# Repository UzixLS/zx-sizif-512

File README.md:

## Sizif-512
Another CPLD-based ZX Spectrum clone for 48K rubber case with some sweet features.

### Tech specs
* Half-sized PCB for 48K rubber case
* Pentagon, Spectrum 128, Spectrum 48 and Spectrum +3e modes
* Altera EPM1270 CPLD
* Real Z80 in 3.5MHz, 4.4MHz, 5.2MHz, 7MHz (no-wait turbo) and 14MHz (turbo with wait-states) modes
* 512K RAM
* Real AY-3-8910 with switchable stereo ABC/ACB/mono output
* Sega 6-button joystick input; Kempston/Sinclair modes
* Integrated DivMMC and Z-Controller, 1x microSD socket
* PAL and RGB video output (Sega Mini-DIN/9 connector)
* Digital video output header for EGA monitors, VGA scandoublers, etc.
* ULAplus
* Timex MultiColor and HiRes support
* Mono covox (Pentagon ans SpecDrum standards)
* SounDrive (4-channel stereo covox)
* WiFi addon ([link](https://github.com/UzixLS/zx-sizif-512-wifi))
* Tape input via 3.5" jack and Bluetooth
* 9-12V power supply with any polarity
* Reset and Magic buttons; header for power button

With extension board ([link](https://github.com/UzixLS/zx-sizif-512-ext)) more features may be added:
* Turbo Sound FM
* General Sound (12MHz / 512Kb RAM)
* SAA1099
* MIDI sound

### Demonstration
Running Pentagon and Spectrum 128 demos: [link](https://www.youtube.com/watch?v=_RoLKcfJSTY) \
Playing music from SD: [link](https://www.youtube.com/watch?v=TmikKD3yqOU) \
Some random photos: [link](https://cloud.err200.net/index.php/s/73TR85tYZkMm8Ax?path=%2Fsizif-512) \
Review by Martin's 8-bit blog (in czech): [link](https://www.8bity.cz/2020/zx-spectrum-clone-with-cpld-ulaplus-sizif-512/#) \
Review by The Retro Shack youtube channel: [link](https://www.youtube.com/watch?v=l5IgQTgq_bg) \
Building from scratch experience in Terence Ang's blog: [part1](https://www.terenceang.com/2021/08/28/building-a-zx-spectrum-clone-in-2021-begining/) [part2](https://www.terenceang.com/2021/08/29/building-a-zx-spectrum-clone-in-2021-sourcing-for-parts/) [part3](https://www.terenceang.com/2021/08/31/building-a-zx-spectrum-clone-in-2021-populating-the-board/)

### Magic button
Sizif has a number of configurable parameters that you can change on the fly. To do this just hold Magic button for a second.

To navigate menu you can use up-down keys, to change value use enter or left-right keys. Kempston, Sinclair, Cursor and QAOP supported.

If you press Magic button for a short time, the standard NMI handler 'll be called.

### Sega gamepad buttons
Sega gamepad support will be available starting from PCB rev.D (or Rev.C with slight modifications).
| Button | Function in Kempston mode | Function in Sinclair mode |
| - | - | - |
| Right | Right (bit 0) | 7 |
| Left | Left (bit 1) | 6 |
| Down | Down (bit 2) | 8 |
| Up | Up (bit 3) | 9 |
| A | Button 3 (bit 6) | N |
| B | Button 1 (bit 4) | 0 |
| C | Button 2 (bit 5) | M |
| X | Turbo Button 3 (bit 6) | Turbo N |
| Y | Turbo Button 1 (bit 4) | Turbo 0 |
| Z | Turbo Button 2 (bit 5) | Turbo M |
| Start | Pause | Pause |
| Mode | Magic button | Magic button |

### PS/2 keyboard buttons
| Button | Function |
| - | - |
| F1 | Pause |
| F2 | Fast forward |
| F5 | Magic button |
| F10 | Reboot |
| F12 | Reboot |
| Ctrl+Alt+Del | Reboot |
| Ctrl+Alt+Backspace | Reboot |
| Numpad 8, 2/5, 4, 6 | Joystick's up-down-left-right |
| Numpad 0/Enter | Joystick's fire |
| Alt | Joystick's fire |

### RAM
Sizif contains 512K RAM. There are two cases how to access it:
1. DivMMC enabled (SD card insert) - 128K available via 7FFDh port, 128K via DFFDh (Profi standart, most compatible with old 128K software) and 128K reserved for DivMMC.
2. No SD card present - 128K available via 7FFDh and 384K via DFFDh. Please note: ULAplus and Magic button shares one page of memory with DFFD port. If you run 512K-software, it's good idea not to use ULAplus and Magic.

Note that DFFDh port available only in Pentagon mode.

### SD card
Sizif have preinstalled esxDOS firmware, which provides ability to load TAP, TRD, SCL, Z80 files and save snapshots. To use this you should format SD cart to FAT32 or FAT16 and unpack latest esxDOS release ([link](http://www.esxdos.org/index.html)) to card. Also it's recommended to install Long Filename Browser ([link](https://spectrumcomputing.co.uk/forums/viewtopic.php?t=2553)) to card.

### Timex 2048 MultiColor and HiRes support
The Timex graphics modes added by amsoft78.
Basic ways to setup Timex 2048 modes is:
* OUT 255, 1 - use Timex Screen #1 from 0x6000 instead of 0x4000
* OUT 255, 2 - sets HiColor mode. Screen bitmap is read from 0x4000, but screen attributes are read from 0x6000. Each 8x1 bitmap has separate attributes entry, in opposite to 8x8 in regular Zx Spectrum.
* OUT 255, 6 - sets HiRes mode. Screen is now 512x192 in two colors. Both Screen #0 from 0x4000 (odd columns) and 0x6000 (even columns) contains bitmap. Bits 5 to 3 in port 0xFF defines the ink color common for the whole screen. Background colour is always its binary inversion.
* OUT 255, 0 - sets the regular ZX Spectrum mode.

To activate Timex modes, the followig ports can be used:
* ZX eLeMeNt compatible port 0x9FFD - shadowing original Timex 0xFF port, but with read and write capabilities.
* ULA+ compatible method - on port 0xBF3B and "ModeGrop" (bits 7:6 == "01"). See Ula+ specification, as the values are different than for port 0xFF. Warning! As the lot of software first sets the Timex mode by 0xFF, and then sets "01000000" value in 0xBF3B, it would reset Timex mode back to 0. So this combination is ignored - no possibiity to turn off Timex modes via Ula+ port.
* oryginal Timex 0xFF port - write only. This preserves original ZX Spectrum "Floating Bus", so the port is write-only.

Warning! The method of binary "or" current 0xFF port value, somewhere adviced to use on original Timex 2048, will not work properly:

```
in      a, (0xFF)
or      a, 2
out     (0xFF), a
```

### Tested addons
* [AYX-32](https://github.com/tslabs/arm/tree/master/AYX-32) - OK
* BDI-ZX ver 2.0 MVcomp FDD interface - OK
* [ZX Dandanator! Mini 2.1](http://www.dandare.es/Proyectos_Dandare/ZX_Dandanator%21_Mini_EN.html) - OK
* [ZX TSid](https://github.com/UzixLS/zx-tsid) - OK
* [Multiface 128 1.00 by Steve Smith](http://projectspeccy.com/projects/) - OK (if SD card isn't insert)
* Noname +3DOS floppy controller - OK (since rev.D)
* [PLUS 2A FDD Interface](https://github.com/konkotgit/PLUS-2A-FDD) - OK (since rev.D)
* DivIDE 5.7d - OK (if SD card isn't insert)
* DMA 2.02 by ShamaZX - OK
* [Kempston + TurboSound interface](https://github.com/konkotgit/KTS) - OK
* [ZX-HD](https://www.bytedelight.com/?page_id=1800) - OK
* [ZX-VGA-JOY](http://zx-vga-joy.com/) - OK
* [Spectranet by ByteDelight](https://www.bytedelight.com/?page_id=3515) - OK
* Spectranet by ShamaZX (aka ZX Net 512) - OK
* ZXKit1 VGA converter (with [alternative firmware](https://github.com/UzixLS/zxkit1-vga-scandoubler-firmware)) - OK

### Changelog & current status
* Rev.A - first release. Please note the [errata](pcb/rev.A/ERRATA.ru.txt) (in russian).
* Rev.B - abandoned. Files kept for historical reason.
* Rev.C - BDI has been removed; improved video circuit; more capable CPLD; better power circuit; add mono AY mode. [Errata](pcb/rev.C/ERRATA.txt).
* Rev.C1 - fixed incorrect JTAG pinout; fixed incorrect silkscreen for power connector J3, tuned some circuit values. Everything seems to work. [Errata](pcb/rev.C1/ERRATA.txt).
* Rev.D:
    * added zxbus connector for in-case addons
    * added support for +3DOS floppy controller
    * added support for Sega 3/6-button gamepad
    * added PS/2
    * added Bluetooth tape input (via M18 module)
    * added alternative microSD card socket footprint
    * fixed compatibility with some keyboards
    * modified tape input circuit
* Rev.D1: minor changes in pcb layout
* Rev.E:
    * added fuse on power input
    * added protection diode on 5V power rail
    * rotated left keyboard connector by 180 degrees
    * replaced TRS audio connectors by TRRS with video output
    * changed C37,C38,C39 footprint to able to install film capacitors
    * improved compatibility with wireless sega gamepads - 3.3V power replaced by 5V
    * added ability to simultaneously install the power/reset keys together with the connectors
    * added jumper for wiring minidin-9 pin 4 with composite or sync output for compatibility with dirty scart cables
    * added ability to install full-height 4.43MHz crystal
    * all 0.5/0.3 vias replaced by 0.6/0.3
    * experimental: 74HCU04-based speaker amplifier replaced by LM386-based
    * experimental: 74HCU04-based tape input circuit replaced by LM311-based
    * experimental: 74HCU04-based crystal clock generator replaced by ICS501-based
* Rev.E1:
    * reverted experimental rev.E changes

### Acknowledgments
This work is inspired and based on a lot of other projects and would hardly have been successful without them:
* Harlequin ([link](https://www.facebook.com/groups/349470902442395/))
* Karabas-128 ([link](https://github.com/andykarpov/karabas-128))
* ZX Evolution ([link](http://nedopc.com/zxevo/zxevo.php))
* zx_ula verilog implementation ([link](https://opencores.org/projects/zx_ula))

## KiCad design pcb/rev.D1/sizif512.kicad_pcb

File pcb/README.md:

* Rev.A - please see [errata (in russian)](rev.A/ERRATA.ru.txt)
* Rev.B - work in progress

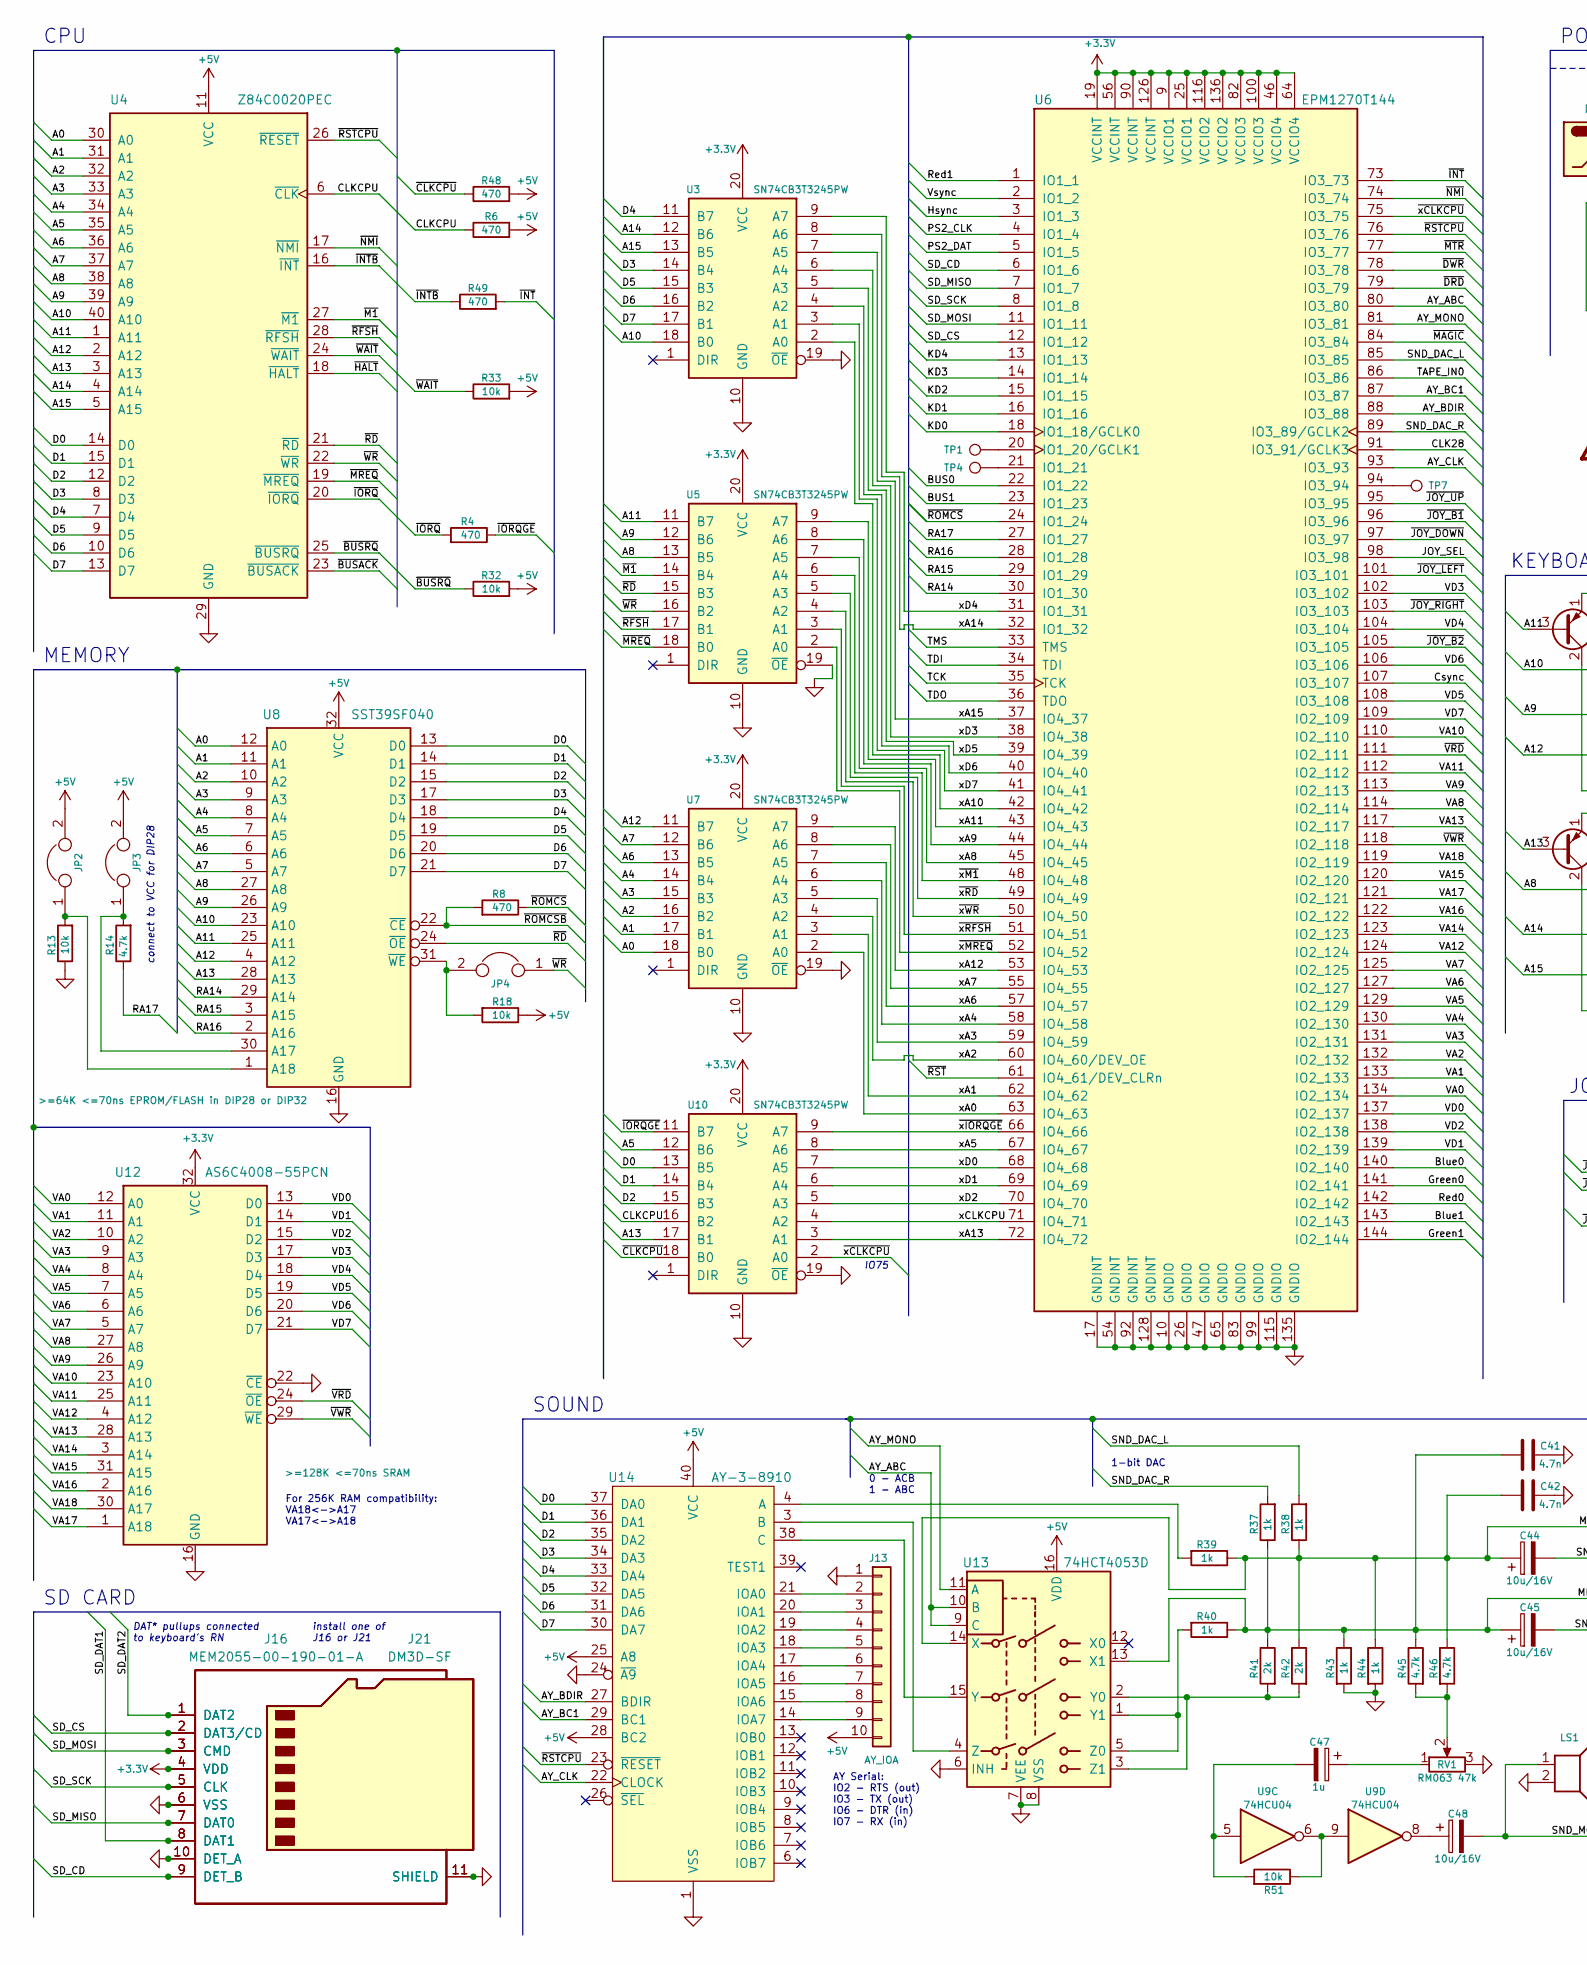
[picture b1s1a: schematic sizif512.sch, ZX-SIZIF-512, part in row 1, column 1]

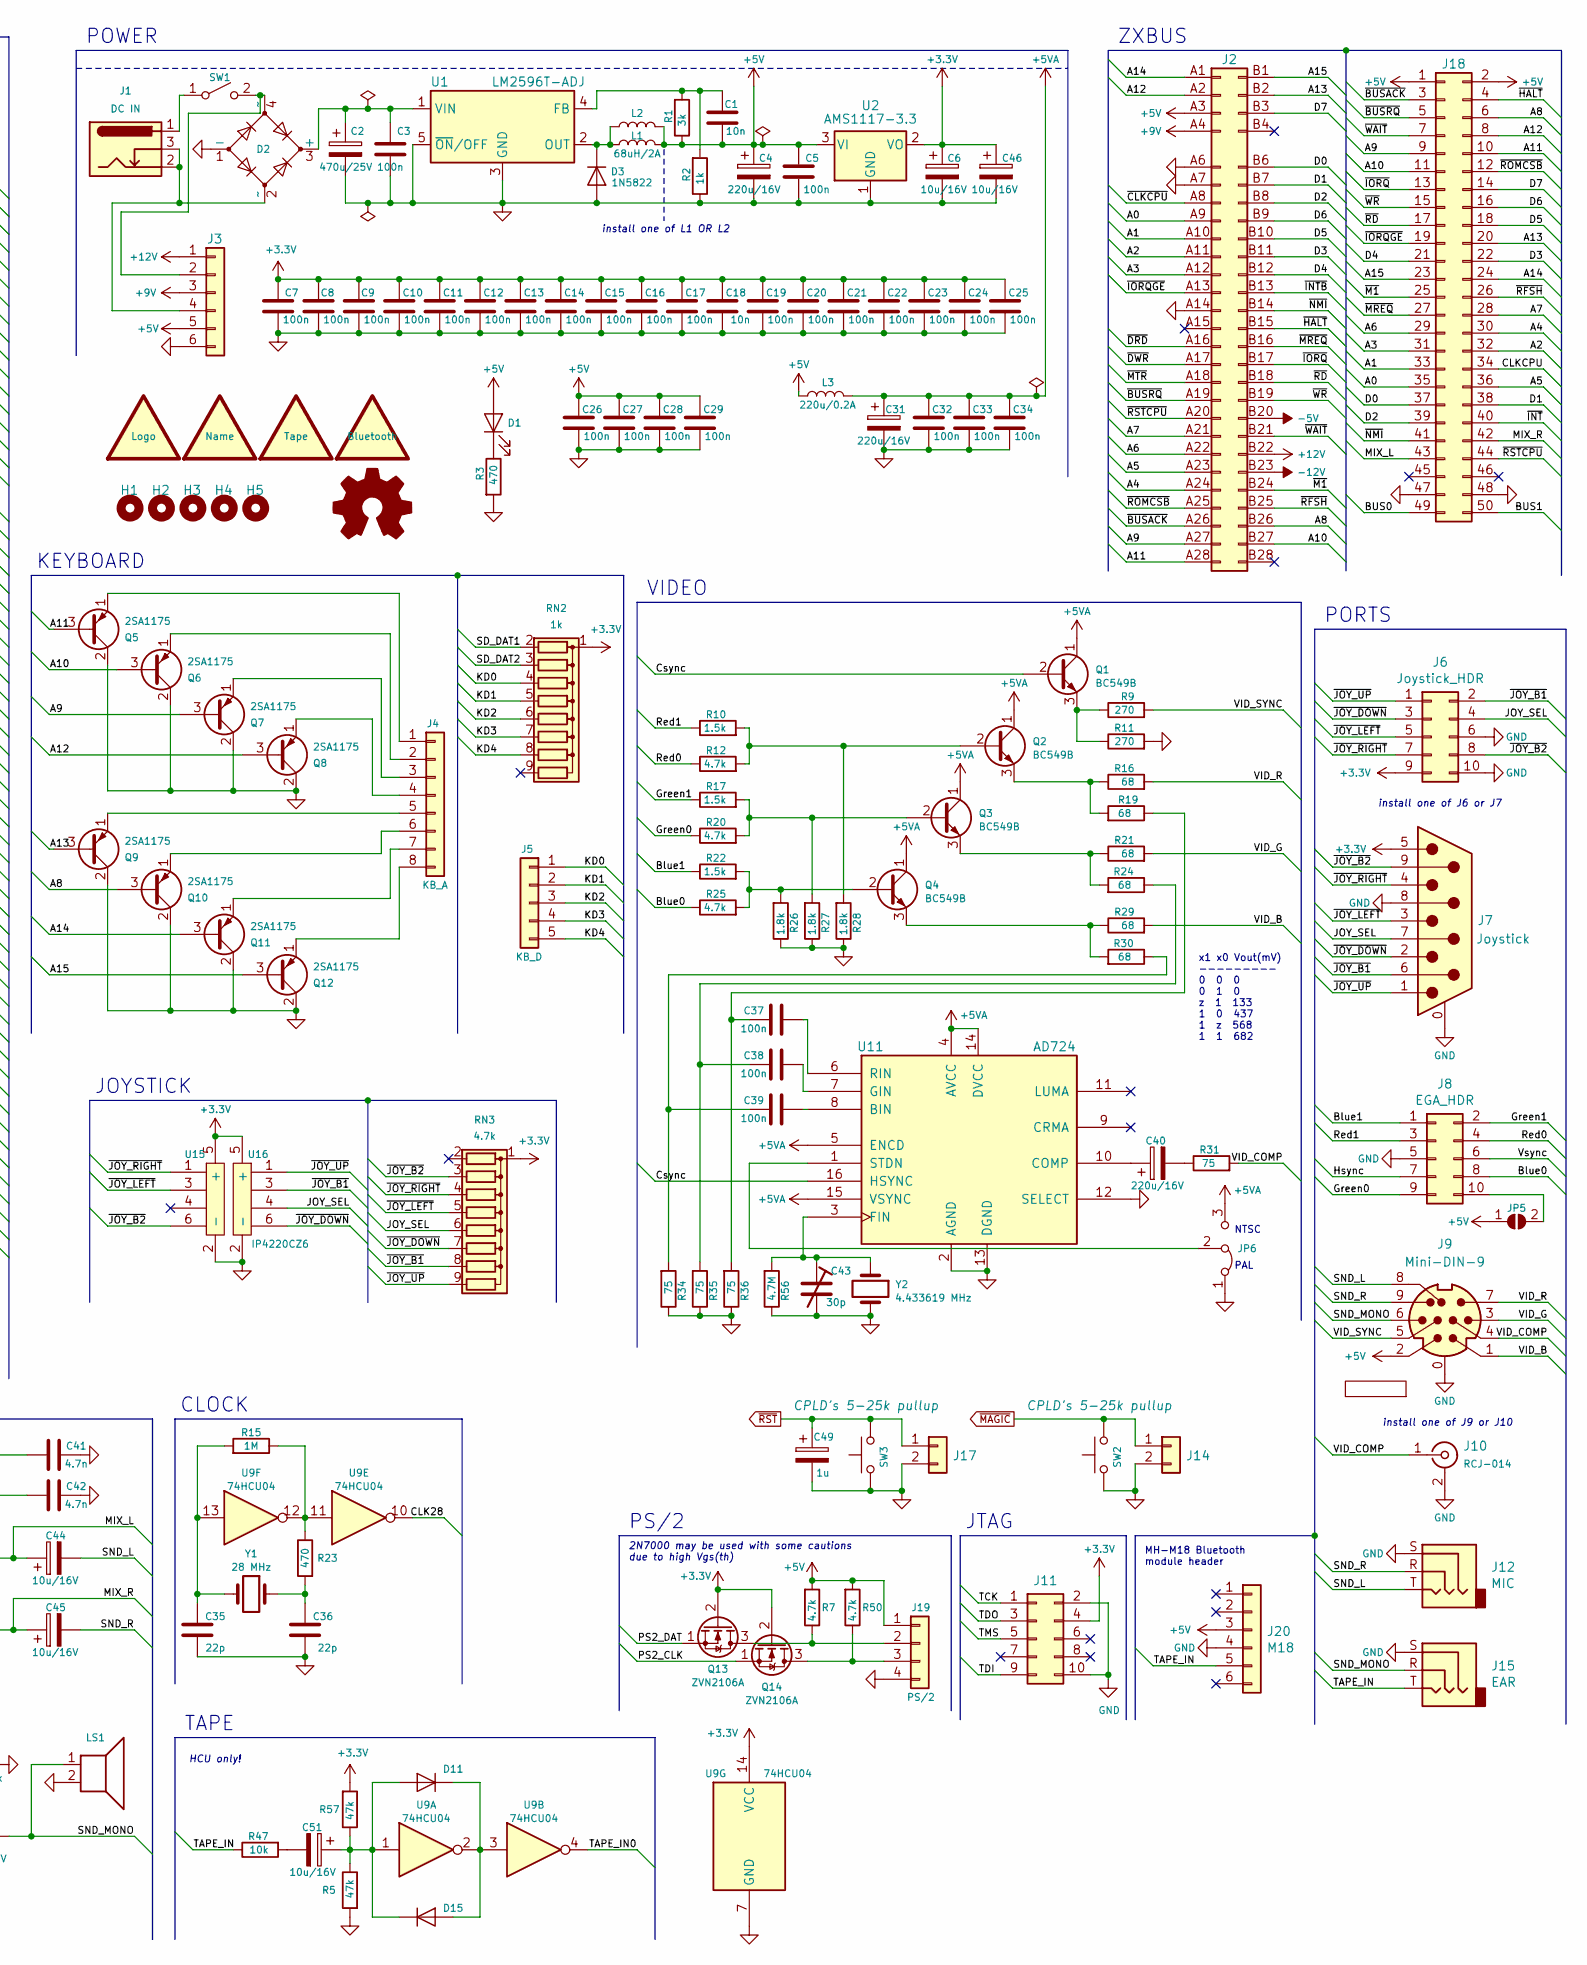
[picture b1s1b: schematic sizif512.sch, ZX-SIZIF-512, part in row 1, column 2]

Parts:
C1: 10n; C_Disc_D5.0mm_W2.5mm_P2.50mm
C2: 470u/25V; CP_Radial_D10.0mm_P5.00mm
C3, C7, C26, C28, C32, C33, C34, C37, C38, C39: 100n; C_Disc_D5.0mm_W2.5mm_P2.50mm
C4, C31: 220u/16V; CP_Radial_D8.0mm_P3.50mm
C5, C8, C9, C10, C11, C12, C13, C14, C15, C16, C17, C19, C20, C21, C22, C23, C24, C25, C27, C29: 100n; C_0805_2012Metric_Pad1.15x1.40mm_HandSolder
C6, C44, C45, C46, C48, C51: 10u/16V; CP_Radial_D5.0mm_P2.00mm
C18: 10n; C_0805_2012Metric_Pad1.15x1.40mm_HandSolder
C35, C36: 22p; C_Disc_D3.8mm_W2.6mm_P2.50mm
C40: 220u/16V; CP_Radial_D6.3mm_P2.50mm
C41, C42: 4.7n; C_Disc_D5.0mm_W2.5mm_P2.50mm
C43: 30p; C_Trim_D6.3mm_P5.50mm
C47, C49: 1u; CP_Radial_D4.0mm_P2.00mm
D1: LED; LED_D4.0mm
D2: 2W10; Diode_Bridge_Round_D10.0mm
D3: 1N5822; D_DO-201AD_P5.08mm_Vertical_AnodeUp
D11, D15: 1N4148; D_DO-35_SOD27_P2.54mm_Vertical_AnodeUp
H1, H2: MountingHole; MountingHole_5mm_7mm_fence
H3, H4, H5: MountingHole; MountingHole_3mm
J1: DS-210; BarrelJack_Horizontal
J2: Conn_02x28_Row_Letter_First; ZX_EDGE
J3, J20: Pin header 1x6 Pitch=2.54mm; PinHeader_1x06_P2.54mm_Vertical
J4: DS1020-08; FFC_FPC_1x08
J5: DS1020-05; FFC_FPC_1x05
J6, J8, J11: Pin header 2x5 Pitch=2.54mm; PinHeader_2x05_P2.54mm_Vertical
J7: DB9-M; DSUB-9_Male_Horizontal_P2.77x2.84mm_EdgePinOffset4.94mm_Hou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
J9: Mini-DIN-9; minidin-9
J10: RCJ-014; CUI_RCJ-01X-WIDE
J12, J15: PJ-313
J13: Pin header 1x10 Pitch=2.54mm; PinHeader_1x10_P2.54mm_Vertical
J14, J17: Pin header 1x2 Pitch=2.54mm; PinHeader_2x01_P2.54mm_Vertical
J16: MEM2055-00-190-01-A; GCT-MEM2055-00-190-01-A
J18: Pin socket 3x25 or 2xPin socket 1x25 Pitch=1.27mm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; PinHeader_2x25_P1.27mm_Edge_SMD
J19: Pin header 1x4 Pitch=2.54mm; PinHeader_1x04_P2.54mm_Vertical
J21: DM3D-SF; microSD_HC_Hirose_DM3D-SF
JP2, JP3, JP4: Jumper / Pin header 1x2 Pitch=2.54mm; PinHeader_1x02_P2.54mm_Vertical
JP5: SolderJumper_2_Open; SolderJumper-2_P1.3mm_Open_RoundedPad1.0x1.5mm
JP6: Jumper_3_Bridged12; SolderJumper-3_P1.3mm_Bridged12_RoundedPad1.0x1.5mm_NumberL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
L1: 68uH/2A; L_Radial_D8.7mm_P5.00mm_Fastron_07HCP
L2: 68uH/2A; L_12x12mm_H8mm
L3: 220u/0.2A; L_Radial_D8.7mm_P5.00mm_Fastron_07HCP
LOGO1: graphic; black-mage2
LOGO2: Logo_Open_Hardware_Small; OSHW-Symbol_6.7x6mm_SilkScreen
LOGO3: graphic; jack35
LOGO4: graphic; bluetooth_small
LOGO5: graphic; sizif512
LS1: Pin header 1x2 Pitch=2.54mm; PinHeader_1x02_P2.54mm_Vertical
Q1, Q2, Q3, Q4: BC549B; TO-92
Q5, Q6, Q7, Q8, Q9, Q10, Q11, Q12: 2SA1175; TO-92S
Q13, Q14: ZVN2106A; TO-92
R1: 3k; R_Axial_DIN0207_L6.3mm_D2.5mm_P2.54mm_Vertical
R2: 1k; R_Axial_DIN0207_L6.3mm_D2.5mm_P2.54mm_Vertical
R3, R23: 470; R_Axial_DIN0207_L6.3mm_D2.5mm_P2.54mm_Vertical
R4, R6, R8, R48, R49: 470; R_Axial_DIN0207_L6.3mm_D2.5mm_P7.62mm_Horizontal
R5, R57: 47k; R_Axial_DIN0207_L6.3mm_D2.5mm_P2.54mm_Vertical
R7, R12, R20, R25, R50: 4.7k; R_Axial_DIN0207_L6.3mm_D2.5mm_P2.54mm_Vertical
R9, R11: 270; R_Axial_DIN0207_L6.3mm_D2.5mm_P2.54mm_Vertical
R10, R17, R22: 1.5k; R_Axial_DIN0207_L6.3mm_D2.5mm_P2.54mm_Vertical
R13, R18, R32, R33: 10k; R_Axial_DIN0207_L6.3mm_D2.5mm_P7.62mm_Horizontal
R14, R45, R46: 4.7k; R_Axial_DIN0207_L6.3mm_D2.5mm_P7.62mm_Horizontal
R15: 1M; R_Axial_DIN0207_L6.3mm_D2.5mm_P2.54mm_Vertical
R16, R19, R21, R24, R29, R30: 68; R_Axial_DIN0207_L6.3mm_D2.5mm_P2.54mm_Vertical
R26, R27, R28: 1.8k; R_Axial_DIN0207_L6.3mm_D2.5mm_P2.54mm_Vertical
R31, R34, R35, R36: 75; R_Axial_DIN0207_L6.3mm_D2.5mm_P2.54mm_Vertical
R37, R38, R39, R40, R43, R44: 1k; R_Axial_DIN0207_L6.3mm_D2.5mm_P7.62mm_Horizontal
R41, R42: 2k; R_Axial_DIN0207_L6.3mm_D2.5mm_P7.62mm_Horizontal
R47, R51: 10k; R_Axial_DIN0207_L6.3mm_D2.5mm_P2.54mm_Vertical
R56: 4.7M; R_0805_2012Metric_Pad1.15x1.40mm_HandSolder
RN2: 1k; R_Array_SIP9
RN3: 4.7k; R_Array_SIP9
RV1: RM063 47k; Potentiometer_Runtron_RM-063_Horizontal
SW1: Jumper / Pin header 1x2 Pitch=2.54mm; Molex_KK-254_AE-6410-02A_1x02_P2.54mm_Vertical
SW2, SW3: Button THT; SW_Tactile_SPST_Angled_PTS645Vx83-2LFS
TP1, TP4, TP7: TestPoint; TestPoint_Pad_D1.0mm
U1: LM2596T-ADJ; TO-220-263-5_Horizontal_TabDown
U2: AMS1117-3.3; SOT-223-3_TabPin2
U3, U5, U7, U10: SN74CB3T3245PW; TSSOP-20_4.4x6.5mm_P0.65mm
U4: Z84C0020PEC; DIP-40_W15.24mm_Socket
U6: EPM1270T144; LQFP-144_20x20mm_P0.5mm
U8: SST39SF040; DIP-32_W15.24mm_Socket
U9: 74HCU04; DIP-14_W7.62mm_Socket
U11: AD724; SOIC-16W_7.5x10.3mm_P1.27mm
U12: AS6C4008-55PCN; DIP-32_W15.24mm_Socket
U13: 74HCT4053D; SOIC-16_3.9x9.9mm_P1.27mm
U14: AY-3-8910; DIP-40_W15.24mm_Socket
U15, U16: IP4220CZ6; TSOP-6_1.65x3.05mm_P0.95mm
Y1: 28 MHz; Crystal_HC49-U_Vertical
Y2: 4.433619 MHz; Crystal_HC49-U_Vertical

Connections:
+3V3: C6.1, C7.2, C8.1, C9.1, C10.1, C11.1, C12.1, C13.1, C14.1, C15.1, C16.1, C17.1, C18.1, C19.1, C20.1, C21.1, C22.1, C23.1, C24.2, C25.2, C46.1, J6.9, J7.5, J11.4, J16.4 (VDD), J21.4 (VDD), Q13.2 (G), Q14.2 (G), R57.2, RN2.1 (common), RN3.1 (common), U2.2 (VO), U3.20 (VCC), U5.20 (VCC), U6.9 (VCCIO1), U6.19 (VCCINT), U6.25 (VCCIO1), U6.46 (VCCIO4), U6.56 (VCCINT), U6.64 (VCCIO4), U6.82 (VCCIO3), U6.90 (VCCINT), U6.100 (VCCIO3), U6.116 (VCCIO2), U6.126 (VCCINT), U6.136 (VCCIO2), U7.20 (VCC), U9.14 (VCC), U10.20 (VCC), U12.32 (VCC), U15.5 (+), U16.5 (+)
+5V: C1.1, C4.1, C5.2, C26.2, C27.2, C28.2, C29.2, D1.2 (A), J2.A3 (Pin_a3), J3.5, J9.2, J13.10, J18.1, J18.2, J19.1, J20.3, JP2.2, JP3.2, JP5.1 (A), L1.2, L2.2, L3.1, R1.1, R6.2, R7.2, R18.1, R32.2, R33.2, R48.2, R50.2, U2.3 (VI), U4.11 (VCC), U8.32 (VCC), U13.16 (VDD), U14.25 (A8), U14.28 (BC2), U14.40 (VCC)
+5VA: C31.1, C32.2, C33.2, C34.2, JP6.3 (B), L3.2, Q1.1 (C), Q2.1 (C), Q3.1 (C), Q4.1 (C), U11.4 (AVCC), U11.5 (ENCD), U11.14 (DVCC), U11.15 (VSYNC)
+9V: J2.A4 (Pin_a4), J3.3
+12V: J2.B22 (Pin_b22), J3.1
/A0: J2.A9 (Pin_a9), J18.35, U4.30 (A0), U7.18 (B0), U8.12 (A0)
/A1: J2.A10 (Pin_a10), J18.33, U4.31 (A1), U7.17 (B1), U8.11 (A1)
/A2: J2.A11 (Pin_a11), J18.32, U4.32 (A2), U7.16 (B2), U8.10 (A2)
/A3: J2.A12 (Pin_a12), J18.31, U4.33 (A3), U7.15 (B3), U8.9 (A3)
/A4: J2.A24 (Pin_a24), J18.30, U4.34 (A4), U7.14 (B4), U8.8 (A4)
/A5: J2.A23 (Pin_a23), J18.36, U4.35 (A5), U8.7 (A5), U10.12 (B6)
/A6: J2.A22 (Pin_a22), J18.29, U4.36 (A6), U7.13 (B5), U8.6 (A6)
/A7: J2.A21 (Pin_a21), J18.28, U4.37 (A7), U7.12 (B6), U8.5 (A7)
/A8: J2.B26 (Pin_b26), J18.6, Q10.3 (B), U4.38 (A8), U5.13 (B5), U8.27 (A8)
/A9: J2.A27 (Pin_a27), J18.9, Q7.3 (B), U4.39 (A9), U5.12 (B6), U8.26 (A9)
/A10: J2.B27 (Pin_b27), J18.11, Q6.3 (B), U3.18 (B0), U4.40 (A10), U8.23 (A10)
/A11: J2.A28 (Pin_a28), J18.10, Q5.3 (B), U4.1 (A11), U5.11 (B7), U8.25 (A11)
/A12: J2.A2 (Pin_a2), J18.8, Q8.3 (B), U4.2 (A12), U7.11 (B7), U8.4 (A12)
/A13: J2.B2 (Pin_b2), J18.20, Q9.3 (B), U4.3 (A13), U8.28 (A13), U10.17 (B1)
/A14: J2.A1 (Pin_a1), J18.24, Q11.3 (B), U3.12 (B6), U4.4 (A14)
/A15: J2.B1 (Pin_b1), J18.23, Q12.3 (B), U3.13 (B5), U4.5 (A15)
/AY_ABC: U6.80 (IO3_80), U13.9 (C), U13.10 (B)
/AY_BC1: U6.87 (IO3_87), U14.29 (BC1)
/AY_BDIR: U6.88 (IO3_88), U14.27 (BDIR)
/AY_CLK: U6.93 (IO3_93), U14.22 (CLOCK)
/AY_MONO: U6.81 (IO3_81), U13.11 (A)
/BUS0: J18.49, U6.22 (IO1_22)
/BUS1: J18.50, U6.23 (IO1_23)
/Blue0: J8.8, R25.1, U6.140 (IO2_140)
/Blue1: J8.1, R22.1, U6.143 (IO2_143)
/CLK28: U6.91 (IO3_91/GCLK3), U9.10
/CLKCPU: J18.34, R6.1, U4.6 (~CLK~), U10.16 (B2)
/Csync: Q1.2 (B), U6.107 (IO3_107), U11.16 (HSYNC)
/D0: J2.B6 (Pin_b6), J18.37, U4.14 (D0), U8.13 (D0), U10.13 (B5), U14.37 (DA0)
/D1: J2.B7 (Pin_b7), J18.38, U4.15 (D1), U8.14 (D1), U10.14 (B4), U14.36 (DA1)
/D2: J2.B8 (Pin_b8), J18.39, U4.12 (D2), U8.15 (D2), U10.15 (B3), U14.35 (DA2)
/D3: J2.B11 (Pin_b11), J18.22, U3.14 (B4), U4.8 (D3), U8.17 (D3), U14.34 (DA3)
/D4: J2.B12 (Pin_b12), J18.21, U3.11 (B7), U4.7 (D4), U8.18 (D4), U14.33 (DA4)
/D5: J2.B10 (Pin_b10), J18.18, U3.15 (B3), U4.9 (D5), U8.19 (D5), U14.32 (DA5)
/D6: J2.B9 (Pin_b9), J18.16, U3.16 (B2), U4.10 (D6), U8.20 (D6), U14.31 (DA6)
/D7: J2.B3 (Pin_b3), J18.14, U3.17 (B1), U4.13 (D7), U8.21 (D7), U14.30 (DA7)
/Green0: J8.9, R20.1, U6.141 (IO2_141)
/Green1: J8.2, R17.1, U6.144 (IO2_144)
/Hsync: J8.7, U6.3 (IO1_3)
/JOY_SEL: J6.4, J7.7, RN3.6 (R5), U6.98 (IO3_98), U16.4
/KD0: J5.1, RN2.4 (R3), U6.18 (IO1_18/GCLK0)
/KD1: J5.2, RN2.5 (R4), U6.16 (IO1_16)
/KD2: J5.3, RN2.6 (R5), U6.15 (IO1_15)
/KD3: J5.4, RN2.7 (R6), U6.14 (IO1_14)
/KD4: J5.5, RN2.8 (R7), U6.13 (IO1_13)
/MIX_L: C42.2, C44.1, J18.43, R38.1, R39.1, R42.1, R44.1, R46.1, U13.14 (X)
/MIX_R: C41.2, C45.1, J18.42, R37.1, R40.1, R41.1, R43.1, R45.1, U13.13 (X1)
/PS2_CLK: Q14.1 (S), U6.4 (IO1_4)
/PS2_DAT: Q13.1 (S), U6.5 (IO1_5)
/RA14: U6.30 (IO1_30), U8.29 (A14)
/RA15: U6.29 (IO1_29), U8.3 (A15)
/RA16: U6.28 (IO1_28), U8.2 (A16)
/RA17: R14.1, U6.27 (IO1_27)
/Red0: J8.4, R12.1, U6.142 (IO2_142)
/Red1: J8.3, R10.1, U6.1 (IO1_1)
/SD_CD: J16.9 (DET_B), J21.9 (DET_B), U6.6 (IO1_6)
/SD_CS: J16.2 (DAT3/CD), J21.2 (DAT3/CD), U6.12 (IO1_12)
/SD_DAT1: J16.8 (DAT1), J21.8 (DAT1), RN2.2 (R1)
/SD_DAT2: J16.1 (DAT2), J21.1 (DAT2), RN2.3 (R2)
/SD_MISO: J16.7 (DAT0), J21.7 (DAT0), U6.7 (IO1_7)
/SD_MOSI: J16.3 (CMD), J21.3 (CMD), U6.11 (IO1_11)
/SD_SCK: J16.5 (CLK), J21.5 (CLK), U6.8 (IO1_8)
/SND_DAC_L: R38.2, U6.85 (IO3_85)
/SND_DAC_R: R37.2, U6.89 (IO3_89/GCLK2)
/SND_L: C44.2, J9.8, J12.T
/SND_MONO: C48.2, J9.6, J15.R, LS1.1
/SND_R: C45.2, J9.9, J12.R
/TAPE_IN: J15.T, J20.5, R47.1
/TAPE_IN0: U6.86 (IO3_86), U9.4
/TCK: J11.1, U6.35 (TCK)
/TDI: J11.9, U6.34 (TDI)
/TDO: J11.3, U6.36 (TDO)
/TMS: J11.5, U6.33 (TMS)
/VA0: U6.134 (IO2_134), U12.12 (A0)
/VA1: U6.133 (IO2_133), U12.11 (A1)
/VA2: U6.132 (IO2_132), U12.10 (A2)
/VA3: U6.131 (IO2_131), U12.9 (A3)
/VA4: U6.130 (IO2_130), U12.8 (A4)
/VA5: U6.129 (IO2_129), U12.7 (A5)
/VA6: U6.127 (IO2_127), U12.6 (A6)
/VA7: U6.125 (IO2_125), U12.5 (A7)
/VA8: U6.114 (IO2_114), U12.27 (A8)
/VA9: U6.113 (IO2_113), U12.26 (A9)
/VA10: U6.110 (IO2_110), U12.23 (A10)
/VA11: U6.112 (IO2_112), U12.25 (A11)
/VA12: U6.124 (IO2_124), U12.4 (A12)
/VA13: U6.117 (IO2_117), U12.28 (A13)
/VA14: U6.123 (IO2_123), U12.3 (A14)
/VA15: U6.120 (IO2_120), U12.31 (A15)
/VA16: U6.122 (IO2_122), U12.2 (A16)
/VA17: U6.121 (IO2_121), U12.1 (A18)
/VA18: U6.119 (IO2_119), U12.30 (A17)
/VD0: U6.137 (IO2_137), U12.13 (D0)
/VD1: U6.139 (IO2_139), U12.14 (D1)
/VD2: U6.138 (IO2_138), U12.15 (D2)
/VD3: U6.102 (IO3_102), U12.17 (D3)
/VD4: U6.104 (IO3_104), U12.18 (D4)
/VD5: U6.108 (IO3_108), U12.19 (D5)
/VD6: U6.106 (IO3_106), U12.20 (D6)
/VD7: U6.109 (IO2_109), U12.21 (D7)
/VID_B: J9.1, R29.2
/VID_COMP: J9.4, J10.1 (In), R31.2
/VID_G: J9.3, R21.2
/VID_R: J9.7, R16.2
/VID_SYNC: J9.5, R9.2
/Vsync: J8.6, U6.2 (IO1_2)
/xA0: U6.63 (IO4_63), U7.2 (A0)
/xA1: U6.62 (IO4_62), U7.3 (A1)
/xA2: U6.60 (IO4_60/DEV_OE), U7.4 (A2)
/xA3: U6.59 (IO4_59), U7.5 (A3)
/xA4: U6.58 (IO4_58), U7.6 (A4)
/xA5: U6.67 (IO4_67), U10.8 (A6)
/xA6: U6.57 (IO4_57), U7.7 (A5)
/xA7: U6.55 (IO4_55), U7.8 (A6)
/xA8: U5.7 (A5), U6.45 (IO4_45)
/xA9: U5.8 (A6), U6.44 (IO4_44)
/xA10: U3.2 (A0), U6.42 (IO4_42)
/xA11: U5.9 (A7), U6.43 (IO4_43)
/xA12: U6.53 (IO4_53), U7.9 (A7)
/xA13: U6.72 (IO4_72), U10.3 (A1)
/xA14: U3.8 (A6), U6.32 (IO1_32)
/xA15: U3.7 (A5), U6.37 (IO4_37)
/xCLKCPU: U6.71 (IO4_71), U10.4 (A2)
/xD0: U6.68 (IO4_68), U10.7 (A5)
/xD1: U6.69 (IO4_69), U10.6 (A4)
/xD2: U6.70 (IO4_70), U10.5 (A3)
/xD3: U3.6 (A4), U6.38 (IO4_38)
/xD4: U3.9 (A7), U6.31 (IO1_31)
/xD5: U3.5 (A3), U6.39 (IO4_39)
/xD6: U3.4 (A2), U6.40 (IO4_40)
/xD7: U3.3 (A1), U6.41 (IO4_41)
/~BUSACK: J2.A26 (Pin_a26), J18.3, U4.23 (~BUSACK~)
/~BUSRQ: J2.A19 (Pin_a19), J18.5, R32.1, U4.25 (~BUSRQ~)
/~CLKCPU: J2.A8 (Pin_a8), R48.1, U10.18 (B0)
/~DRD: J2.A16 (Pin_a16), U6.79 (IO3_79)
/~DWR: J2.A17 (Pin_a17), U6.78 (IO3_78)
/~HALT: J2.B15 (Pin_b15), J18.4, U4.18 (~HALT~)
/~INT: J18.40, R49.2, U6.73 (IO3_73)
/~INTB: J2.B13 (Pin_b13), R49.1, U4.16 (~INT~)
/~IORQ: J2.B17 (Pin_b17), J18.13, R4.2, U4.20 (~IORQ~)
/~IORQGE: J2.A13 (Pin_a13), J18.19, R4.1, U10.11 (B7)
/~JOY_B1: J6.2, J7.6, RN3.8 (R7), U6.96 (IO3_96), U16.3
/~JOY_B2: J6.8, J7.9, RN3.3 (R2), U6.105 (IO3_105), U15.6
/~JOY_DOWN: J6.3, J7.2, RN3.7 (R6), U6.97 (IO3_97), U16.6
/~JOY_LEFT: J6.5, J7.3, RN3.5 (R4), U6.101 (IO3_101), U15.3
/~JOY_RIGHT: J6.7, J7.4, RN3.4 (R3), U6.103 (IO3_103), U15.1
/~JOY_UP: J6.1, J7.1, RN3.9 (R8), U6.95 (IO3_95), U16.1
/~M1: J2.B24 (Pin_b24), J18.25, U4.27 (~M1~), U5.14 (B4)
/~MREQ: J2.B16 (Pin_b16), J18.27, U4.19 (~MREQ~), U5.18 (B0)
/~MTR: J2.A18 (Pin_a18), U6.77 (IO3_77)
/~NMI: J2.B14 (Pin_b14), J18.41, U4.17 (~NMI~), U6.74 (IO3_74)
/~RD: J2.B18 (Pin_b18), J18.17, U4.21 (~RD~), U5.15 (B3), U8.24 (~OE)
/~RFSH: J2.B25 (Pin_b25), J18.26, U4.28 (~RFSH~), U5.17 (B1)
/~ROMCS: R8.1, U6.24 (IO1_24)
/~ROMCSB: J2.A25 (Pin_a25), J18.12, R8.2, U8.22 (~CE)
/~RSTCPU: J2.A20 (Pin_a20), J18.44, U4.26 (~RESET~), U6.76 (IO3_76), U14.23 (~RESET~)
/~VRD: U6.111 (IO2_111), U12.24 (~OE)
/~VWR: U6.118 (IO2_118), U12.29 (~WE)
/~WAIT: J2.B21 (Pin_b21), J18.7, R33.1, U4.24 (~WAIT~)
/~WR: J2.B19 (Pin_b19), J18.15, JP4.1, U4.22 (~WR~), U5.16 (B2)
/~xCLKCPU: U6.75 (IO3_75), U10.2 (A0)
/~xIORQGE: U6.66 (IO4_66), U10.9 (A7)
/~xM1: U5.6 (A4), U6.48 (IO4_48)
/~xMREQ: U5.2 (A0), U6.52 (IO4_52)
/~xRD: U5.5 (A3), U6.49 (IO4_49)
/~xRFSH: U5.3 (A1), U6.51 (IO4_51)
/~xWR: U5.4 (A2), U6.50 (IO4_50)
GND: C2.2, C3.2, C4.2, C5.1, C6.2, C7.1, C8.2, C9.2, C10.2, C11.2, C12.2, C13.2, C14.2, C15.2, C16.2, C17.2, C18.2, C19.2, C20.2, C21.2, C22.2, C23.2, C24.1, C25.1, C26.1, C27.1, C28.1, C29.1, C31.2, C32.1, C33.1, C34.1, C35.1, C36.1, C41.1, C42.1, C43.2, C46.2, C49.2, D2.1 (-), D3.2 (A), J2.A6 (Pin_a6), J2.A7 (Pin_a7), J2.A14 (Pin_a14), J3.6, J6.6, J6.10, J7.0 (PAD), J7.8, J8.5, J9.0, J10.2 (Ext), J11.2, J11.10, J12.S, J13.1, J14.2, J15.S, J16.6 (VSS), J16.10 (DET_A), J16.11 (SHIELD), J17.2, J18.47, J18.48, J19.4, J20.4, J21.6 (VSS), J21.10 (DET_A), J21.11 (SHIELD), JP6.1 (A), LS1.2, Q5.2 (C), Q6.2 (C), Q7.2 (C), Q8.2 (C), Q9.2 (C), Q10.2 (C), Q11.2 (C), Q12.2 (C), R2.1, R3.2, R5.2, R11.2, R13.1, R26.1, R27.1, R28.1, R34.1, R35.1, R36.1, R43.2, R44.2, R56.1, RV1.3, SW2.1, SW3.1, U1.3 (GND), U1.5 (~ON~/OFF), U2.1 (GND), U3.10 (GND), U3.19 (~OE), U4.29 (GND), U5.10 (GND), U5.19 (~OE), U6.10 (GNDIO), U6.17 (GNDINT), U6.26 (GNDIO), U6.47 (GNDIO), U6.54 (GNDINT), U6.65 (GNDIO), U6.83 (GNDIO), U6.92 (GNDINT), U6.99 (GNDIO), U6.115 (GNDIO), U6.128 (GNDINT), U6.135 (GNDIO), U7.10 (GND), U7.19 (~OE), U8.16 (GND), U9.7 (GND), U10.10 (GND), U10.19 (~OE), U11.2 (AGND), U11.12 (SELECT), U11.13 (DGND), U12.16 (GND), U12.22 (~CE), U13.6 (INH), U13.7 (VEE), U13.8 (VSS), U14.1 (VSS), U14.24 (~A9~), U15.2 (-), U16.2 (-), Y2.2
unnamed: C1.2, R1.2, R2.2, U1.4 (FB)
unnamed: C2.1, C3.1, D2.3 (+), U1.1 (VIN)
unnamed: C35.2, R15.2, U9.13, Y1.2
unnamed: C36.2, R23.2, Y1.1
unnamed: C37.1, R19.1, R36.2
unnamed: C37.2, U11.6 (RIN)
unnamed: C38.1, R24.1, R35.2
unnamed: C38.2, U11.7 (GIN)
unnamed: C39.1, R30.1, R34.2
unnamed: C39.2, U11.8 (BIN)
unnamed: C40.1, U11.10 (COMP)
unnamed: C40.2, R31.1
unnamed: C43.1, R56.2, U11.3 (FIN), Y2.1
unnamed: C47.1, RV1.1
unnamed: C47.2, R51.2, U9.5
unnamed: C48.1, U9.8
unnamed: C51.1, D11.2 (A), D15.1 (K), R5.1, R57.1, U9.1
unnamed: C51.2, R47.2
unnamed: D1.1 (K), R3.1
unnamed: D2.2 (~~), J1.2, J1.3, J3.4
unnamed: D2.4 (~~), J3.2, SW1.2 (B)
unnamed: D3.1 (K), L1.1, L2.1, U1.2 (OUT)
unnamed: D11.1 (K), D15.2 (A), U9.2, U9.3
unnamed: J1.1, SW1.1 (A)
unnamed: J4.1, Q5.1 (E)
unnamed: J4.2, Q6.1 (E)
unnamed: J4.3, Q7.1 (E)
unnamed: J4.4, Q8.1 (E)
unnamed: J4.5, Q9.1 (E)
unnamed: J4.6, Q10.1 (E)
unnamed: J4.7, Q11.1 (E)
unnamed: J4.8, Q12.1 (E)
unnamed: J8.10, JP5.2 (B)
unnamed: J13.2, U14.21 (IOA0)
unnamed: J13.3, U14.20 (IOA1)
unnamed: J13.4, U14.19 (IOA2)
unnamed: J13.5, U14.18 (IOA3)
unnamed: J13.6, U14.17 (IOA4)
unnamed: J13.7, U14.16 (IOA5)
unnamed: J13.8, U14.15 (IOA6)
unnamed: J13.9, U14.14 (IOA7)
unnamed: J19.2, Q13.3 (D), R7.1
unnamed: J19.3, Q14.3 (D), R50.1
unnamed: JP2.1, R13.2, U8.1 (A18)
unnamed: JP3.1, R14.2, U8.30 (A17)
unnamed: JP4.2, R18.2, U8.31 (~WE)
unnamed: JP6.2 (C), U11.1 (STDN)
unnamed: Q1.3 (E), R9.1, R11.1
unnamed: Q2.2 (B), R10.2, R12.2, R28.2
unnamed: Q2.3 (E), R16.1, R19.2
unnamed: Q3.2 (B), R17.2, R20.2, R27.2
unnamed: Q3.3 (E), R21.1, R24.2
unnamed: Q4.2 (B), R22.2, R25.2, R26.2
unnamed: Q4.3 (E), R29.1, R30.2
unnamed: R15.1, R23.1, U9.11, U9.12
unnamed: R39.2, U14.4 (A)
unnamed: R40.2, U13.1 (Y1), U13.5 (Z0)
unnamed: R41.2, R42.2, U13.2 (Y0), U13.3 (Z1)
unnamed: R45.2, R46.2, RV1.2
unnamed: R51.1, U9.6, U9.9
unnamed: TP1.1, U6.20 (IO1_20/GCLK1)
unnamed: TP4.1, U6.21 (IO1_21)
unnamed: TP7.1, U6.94 (IO3_94)
unnamed: U13.4 (Z), U14.3 (B)
unnamed: U13.15 (Y), U14.38 (C)
~MAGIC: J14.1, SW2.2, U6.84 (IO3_84)
~RST: C49.1, J17.1, SW3.2, U6.61 (IO4_61/DEV_CLRn)

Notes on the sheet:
CPU
SD CARD
SOUND
0 - ACB 1 - ABC
AY Serial: IO2 - RTS (out) IO3 - TX (out) IO6 - DTR (in) IO7 - RX (in)
For 256K RAM compatibility: VA18<->A17 VA17<->A18
POWER
ZXBUS
CLOCK
MEMORY
1-bit DAC
MH-M18 Bluetooth module header
TAPE
install one of L1 OR L2
install one of J16 or J21
DAT* pullups connected to keyboard's RN
IO75
JTAG
x1 x0 Vout(mV) --------- 0 0 0 0 1 0 z 1 133 1 0 437 1 z 568 1 1 682
NTSC
PAL
VIDEO
PORTS
install one of J9 or J10
install one of J6 or J7
PS/2
KEYBOARD
JOYSTICK
connect to VCC for DIP28
2N7000 may be used with some cautions due to high Vgs(th)
HCU only!

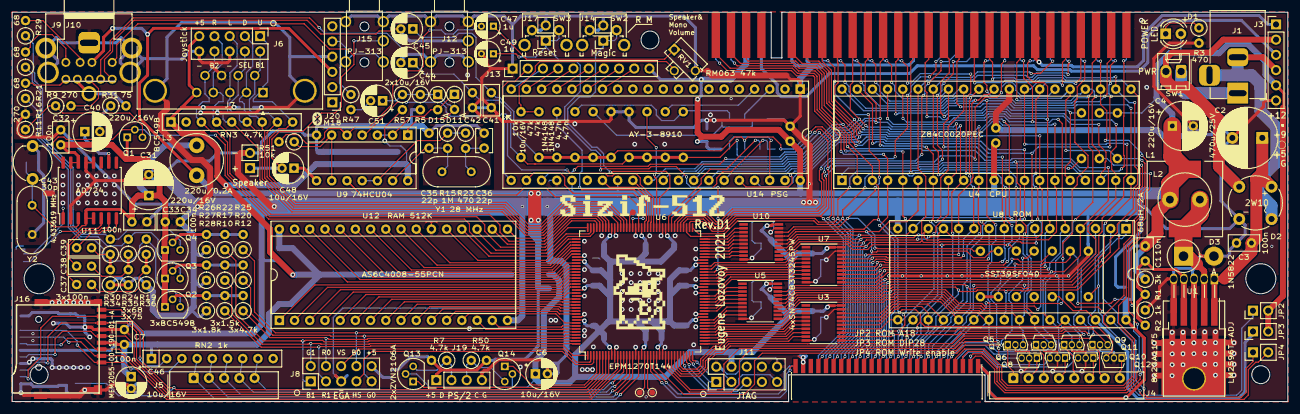
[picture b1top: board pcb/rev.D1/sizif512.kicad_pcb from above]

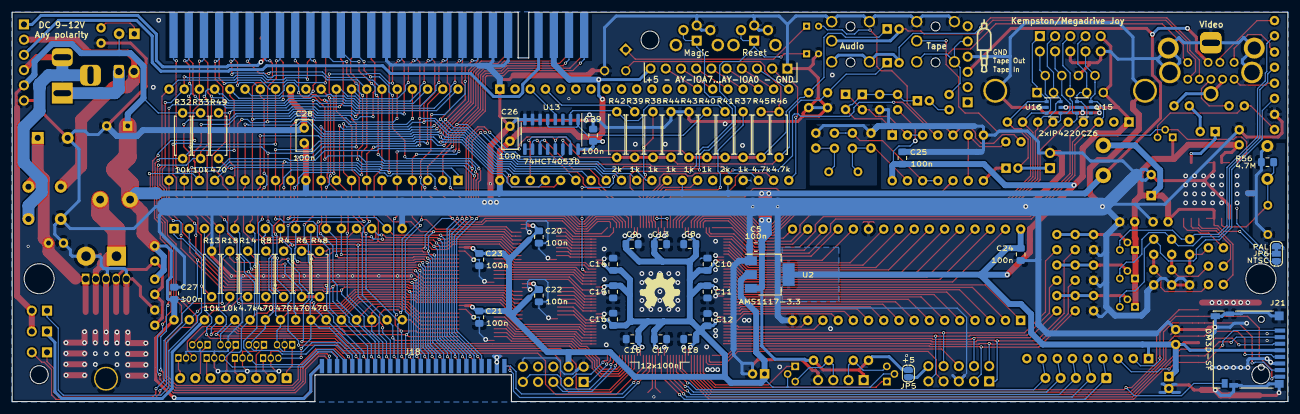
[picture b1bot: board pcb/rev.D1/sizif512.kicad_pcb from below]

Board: 2 copper layers, 213.0 x 65.0 mm, 188 parts (53 on the bottom side), 240 nets.
